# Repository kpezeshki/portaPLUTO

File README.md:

# portaPLUTO
### LINQS Hardware Hack Week 2026

This is a handheld microwave analyzer based on the PlutoSky, a variant of the ADALM-PLUTO SDR development platform. At a hardware level, it consists of a PlutoSky RF PCB, a system board, and user IO. The software integrates with Maia-SDR and iio to deliver basic microwave characterization functionality.

## Hardware

To build a portaPLUTO, you will need the following:

- a PlutoSky board. Buy one without the GPIO header, as you'll want pins of a different height
- a mainboard PCB. JLCPCB stocks most of the components, but minor SMT hand assembly is required
- an aluminum midplate. The Fusion file includes toolpaths for a Makera Carvera, but you can get this manufactured externally. This needs to be aluminum, not plastic, as it is used as a heatsink.
- an 18650 cell. Unprotected is OK. The max discharge you should expect is 1.5 A
- a CH320QV15A-T 3.2" TFT display. Adafruit resells these
- Assorted 3D printed components (backplate, display mount, knob). Some of these have versions intended for machining with toolpaths

## Software

The main software package is built around tezuka and maia-sdr, though rtl_433 and dump1090 are exposed in applications. The software consists of an FPGA image, a Zynq firmware image, and a Pi Pico firmware image: these vary from the tezuka defaults, so ensure you flash both.

Importantly, *the system must be powered before you plug the PlutoSky or Pico in to a computer!*

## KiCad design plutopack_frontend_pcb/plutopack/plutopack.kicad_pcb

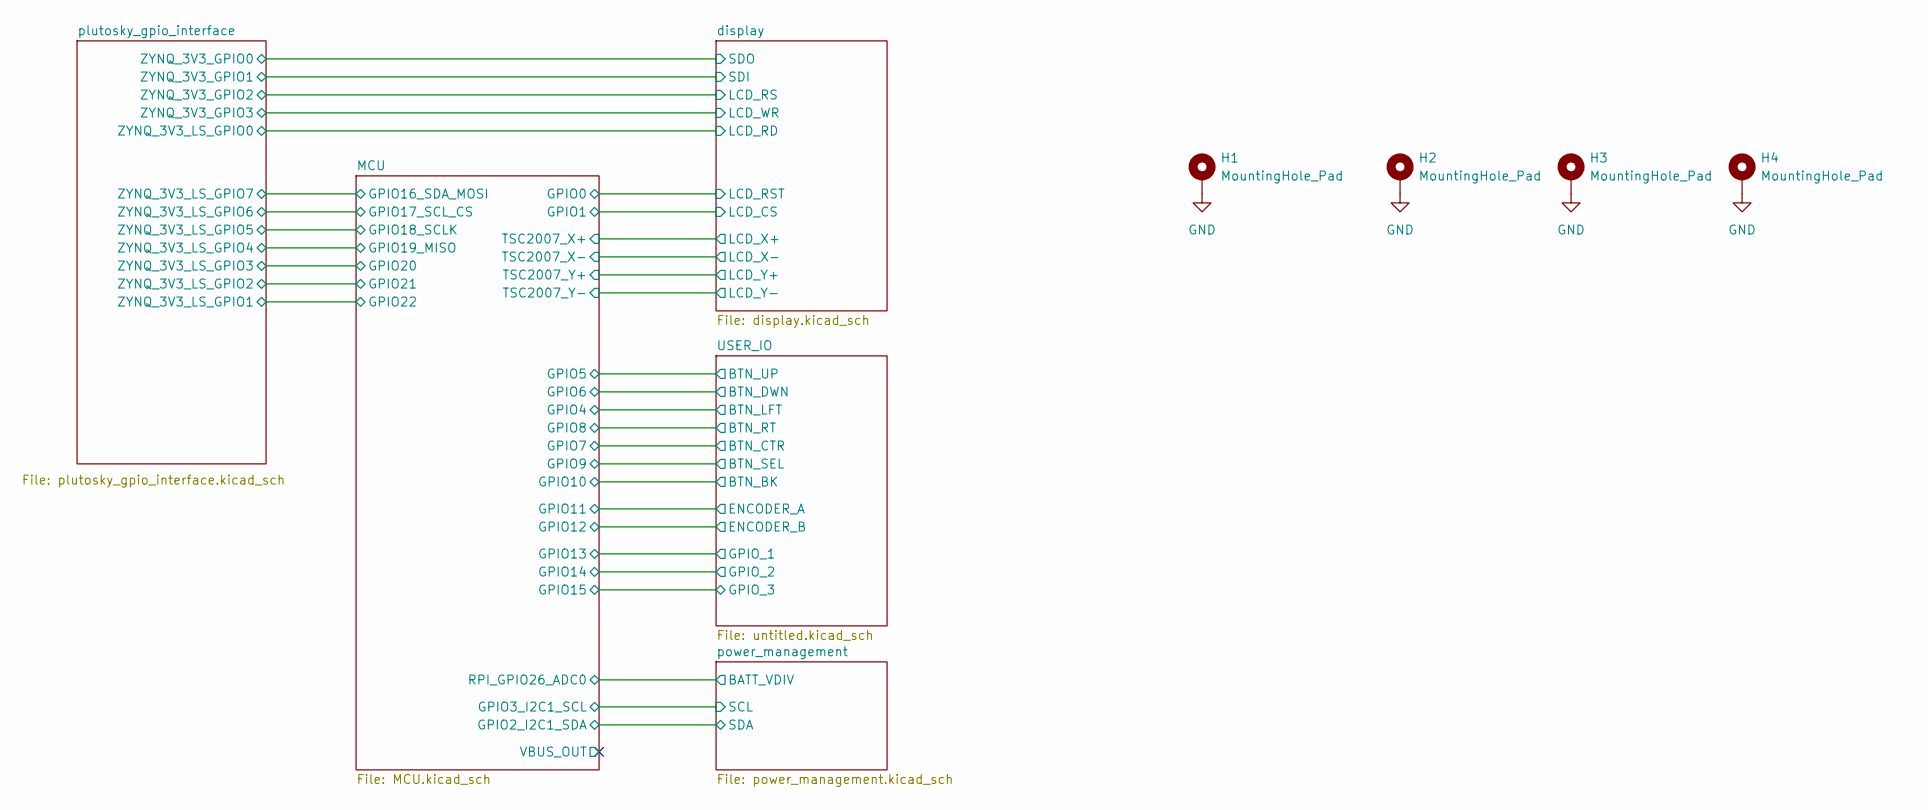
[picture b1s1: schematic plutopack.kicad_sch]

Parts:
H1, H2, H3, H4: MountingHole_Pad; MountingHole_3.2mm_M3_DIN965_Pad

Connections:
GND: H1.1, H2.1, H3.1, H4.1; also elsewhere on the board

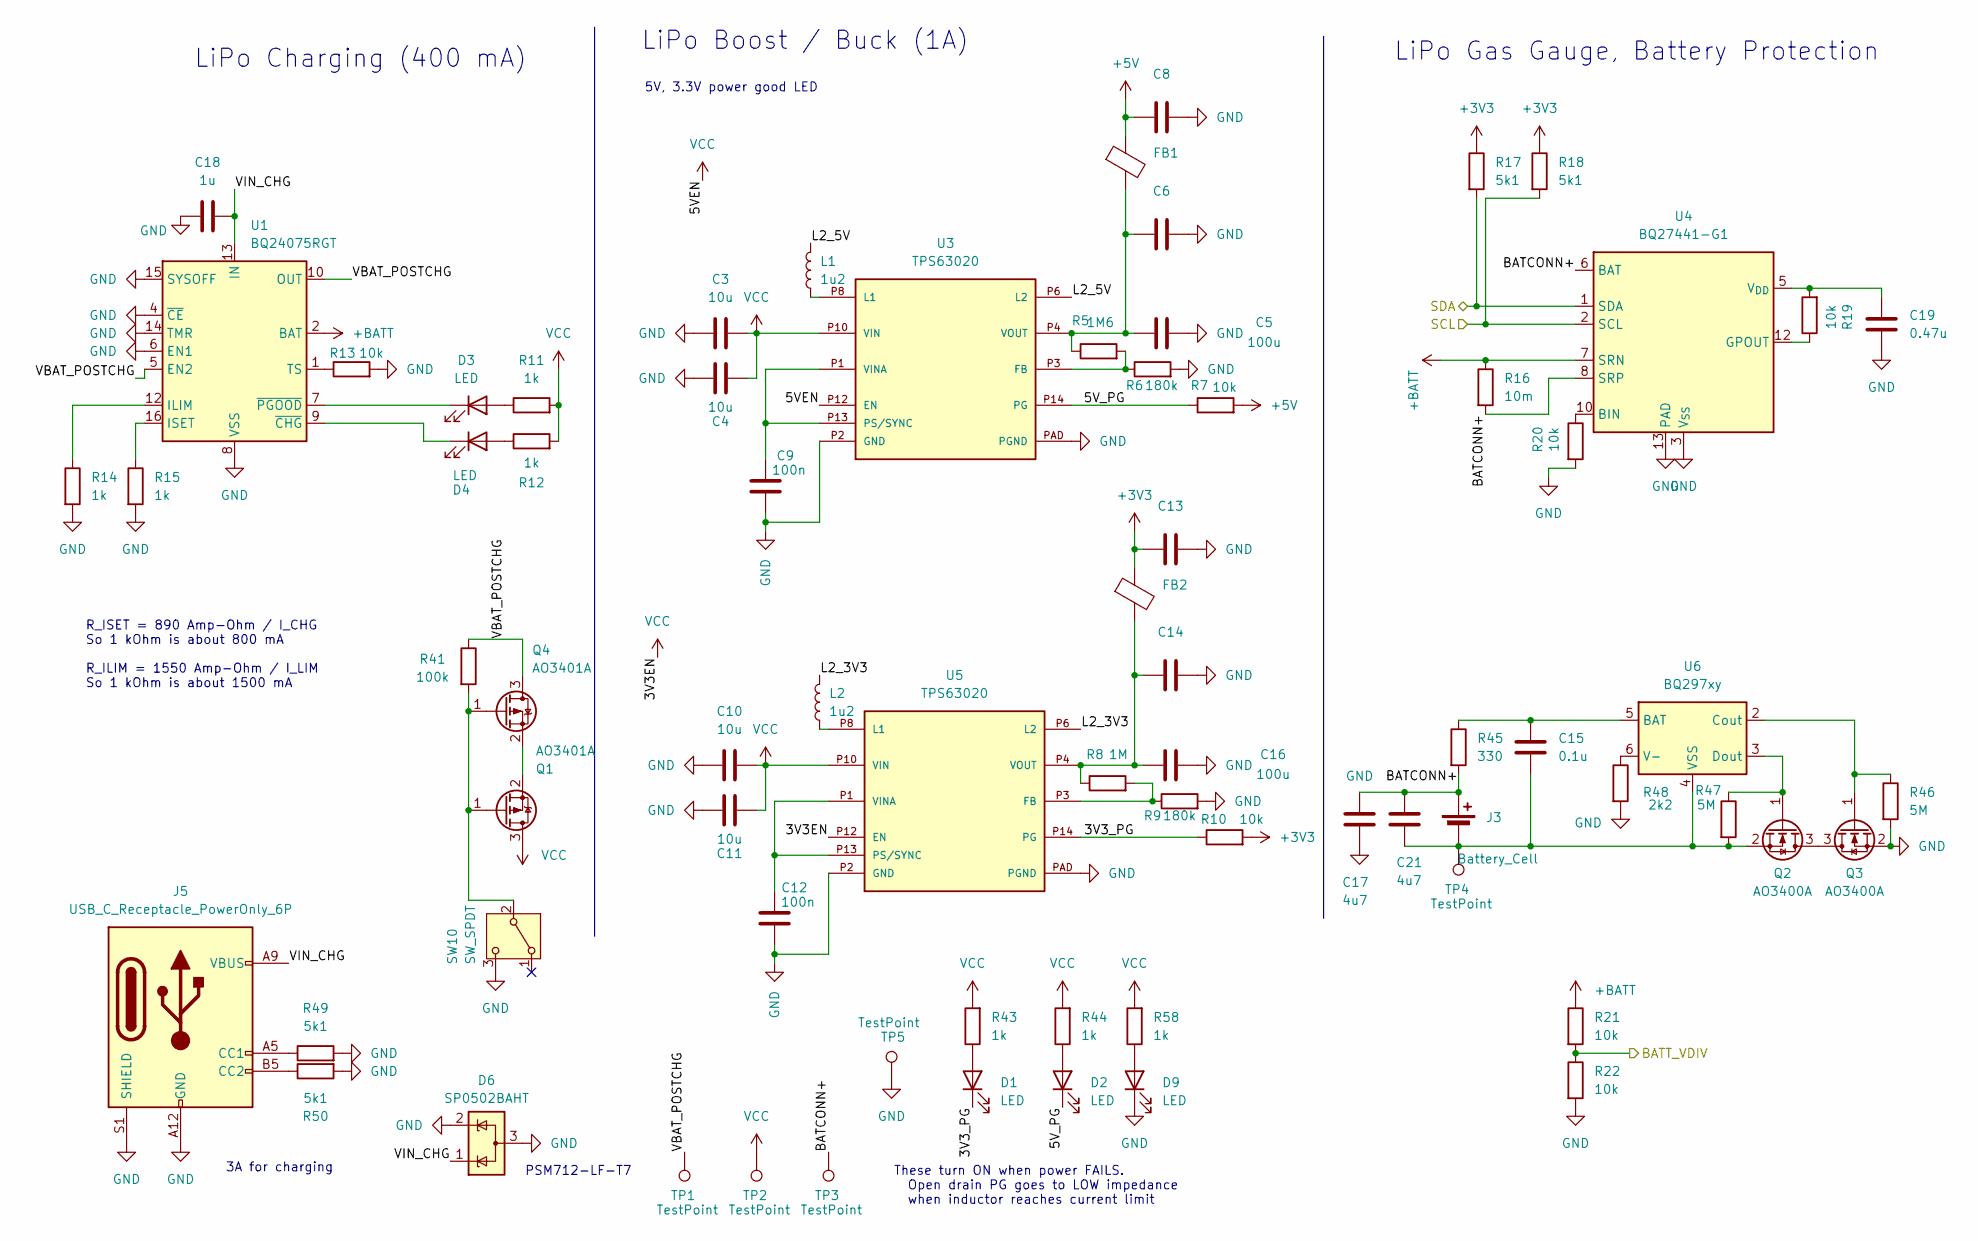
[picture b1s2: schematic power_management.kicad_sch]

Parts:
C3, C4, C10, C11: 10u; C_0603_1608Metric
C5, C16: 100u; CP_EIA-7343-31_Kemet-D
C6, C8, C13, C14: C_0603_1608Metric
C9, C12: 100n; C_0603_1608Metric
C15: 0.1u; C_0603_1608Metric
C17, C21: 4u7; C_0603_1608Metric
C18: 1u; C_0603_1608Metric
C19: 0.47u; C_0603_1608Metric
D1, D2, D3, D4, D9: LED; LED_0603_1608Metric
D6: SP0502BAHT; SOT-23
FB1, FB2: R_0603_1608Metric
J3: Battery_Cell; BatteryHolder_Keystone_1042_1x18650
J5: USB_C_Receptacle_PowerOnly_6P; USB_C_Receptacle_GCT_USB4125-xx-x-0190_6P_TopMnt_Horizontal
L1, L2: 1u2; L_12x12mm_H4.5mm
Q1, Q4: AO3401A; SOT-23
Q2, Q3: AO3400A; SOT-23
R5: 1M6; R_0603_1608Metric
R6, R9: 180k; R_0603_1608Metric
R7, R10, R13, R19, R20, R21, R22: 10k; R_0603_1608Metric
R8: 1M; R_0603_1608Metric
R11, R12, R14, R15, R43, R44, R58: 1k; R_0603_1608Metric
R16: 10m; R_0603_1608Metric
R17, R18, R49, R50: 5k1; R_0603_1608Metric
R41: 100k; R_0603_1608Metric
R45: 330; R_0603_1608Metric
R46, R47: 5M; R_0603_1608Metric
R48: 2k2; R_0603_1608Metric
SW10: SW_SPDT; SW_Slide_SPDT_Straight_CK_OS102011MS2Q
TP1, TP2, TP3, TP4, TP5: TestPoint; TestPoint_THTPad_D1.5mm_Drill0.7mm
U1: BQ24075RGT; VQFN-16-1EP_3x3mm_P0.5mm_EP1.6x1.6mm
U3, U5: TPS63020; QFN14_1
U4: BQ27441-G1; Texas_S-PDSO-N12
U6: BQ297xy; WSON-6_1.5x1.5mm_P0.5mm

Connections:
+3V3: C13.2, FB2.1, R10.2, R17.1, R18.1; also elsewhere on the board
+5V: C8.2, FB1.1, R7.2; also elsewhere on the board
+BATT: R16.1, R21.1, U1.2 (BAT), U1.3 (BAT), U4.7 (SRN)
/MCU/GPIO2_I2C1_SDA: R17.2, U4.1 (SDA); also elsewhere on the board
/MCU/GPIO3_I2C1_SCL: R18.2, U4.2 (SCL); also elsewhere on the board
/MCU/RPI_GPIO26_ADC0: R21.2, R22.1; also elsewhere on the board
/power_management/3V3_PG: D1.1 (K), R10.1, U5.P14 (PG)
/power_management/5V_PG: D2.1 (K), R7.1, U3.P14 (PG)
/power_management/BATCONN+: C17.2, C21.2, J3.1 (+), R16.2, R45.2, TP3.1, U4.6 (BAT), U4.8 (SRP)
/power_management/L2_3V3: L2.2, U5.P6 (L2), U5.P7 (L2)
/power_management/L2_5V: L1.2, U3.P6 (L2), U3.P7 (L2)
/power_management/VBAT_POSTCHG: Q4.3 (D), R41.1, TP1.1, U1.5 (EN2), U1.10 (OUT), U1.11 (OUT)
/power_management/VIN_CHG: C18.2, D6.1 (K), J5.A9 (VBUS), J5.B9 (VBUS), U1.13 (IN)
GND: C3.1, C4.1, C5.1, C6.1, C8.1, C9.1, C10.1, C11.1, C12.1, C13.1, C14.1, C16.1, C17.1, C18.1, C19.1, D6.2 (K), D6.3 (A), D9.1 (K), J5.A12 (GND), J5.B12 (GND), J5.S1 (SHIELD), Q3.2 (S), R6.2, R9.2, R13.2, R14.2, R15.2, R20.2, R22.2, R46.2, R48.2, R49.2, R50.2, SW10.3 (C), TP5.1, U1.4 (~CE), U1.6 (EN1), U1.8 (VSS), U1.14 (TMR), U1.15 (SYSOFF), U1.17 (VSS), U3.P2 (GND), U3.PAD (PGND), U4.3 (V_{SS}), U4.13 (PAD), U5.P2 (GND), U5.PAD (PGND); also elsewhere on the board
unnamed: C5.2, C6.2, FB1.2, R5.1, U3.P4 (VOUT), U3.P5 (VOUT)
unnamed: C14.2, C16.2, FB2.2, R8.1, U5.P4 (VOUT), U5.P5 (VOUT)
unnamed: D1.2 (A), R43.1
unnamed: D2.2 (A), R44.1
unnamed: D3.2 (A), R11.1
unnamed: D3.1 (K), U1.7 (~PGOOD)
unnamed: D4.2 (A), R12.1
unnamed: D4.1 (K), U1.9 (~CHG)
unnamed: D9.2 (A), R58.1
unnamed: C15.2, C21.1, J3.2 (-), Q2.2 (S), R47.2, TP4.1, U6.4 (VSS)
unnamed: J5.A5 (CC1), R49.1
unnamed: J5.B5 (CC2), R50.1
unnamed: L1.1, U3.P8 (L1), U3.P9 (L1)
unnamed: L2.1, U5.P8 (L1), U5.P9 (L1)
unnamed: Q1.1 (G), Q4.1 (G), R41.2, SW10.2 (B)
unnamed: Q1.2 (S), Q4.2 (S)
unnamed: Q2.3 (D), Q3.3 (D)
unnamed: Q2.1 (G), R47.1, U6.3 (Dout)
unnamed: Q3.1 (G), R46.1, U6.2 (Cout)
unnamed: R14.1, U1.12 (ILIM)
unnamed: R15.1, U1.16 (ISET)
unnamed: R13.1, U1.1 (TS)
unnamed: R5.2, R6.1, U3.P3 (FB)
unnamed: C9.2, U3.P1 (VINA), U3.P13 (PS/SYNC)
unnamed: R20.1, U4.10 (BIN)
unnamed: R19.1, U4.12 (GPOUT)
unnamed: C19.2, R19.2, U4.5 (V_{DD})
unnamed: R8.2, R9.1, U5.P3 (FB)
unnamed: C12.2, U5.P1 (VINA), U5.P13 (PS/SYNC)
unnamed: C15.1, R45.1, U6.5 (BAT)
unnamed: R48.1, U6.6 (V-)
VCC: C3.2, C4.2, C10.2, C11.2, Q1.3 (D), R11.2, R12.2, R43.2, R44.2, R58.2, TP2.1, U3.P10 (VIN), U3.P11 (VIN), U3.P12 (EN), U5.P10 (VIN), U5.P11 (VIN), U5.P12 (EN)

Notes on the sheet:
3A for charging
LiPo Gas Gauge, Battery Protection
5V, 3.3V power good LED
LiPo Charging (400 mA)
These turn ON when power FAILS. Open drain PG goes to LOW impedance when inductor reaches current limit
R_ILIM = 1550 Amp-Ohm / I_LIM So 1 kOhm is about 1500 mA
LiPo Boost / Buck (1A)
R_ISET = 890 Amp-Ohm / I_CHG So 1 kOhm is about 800 mA
PSM712-LF-T7

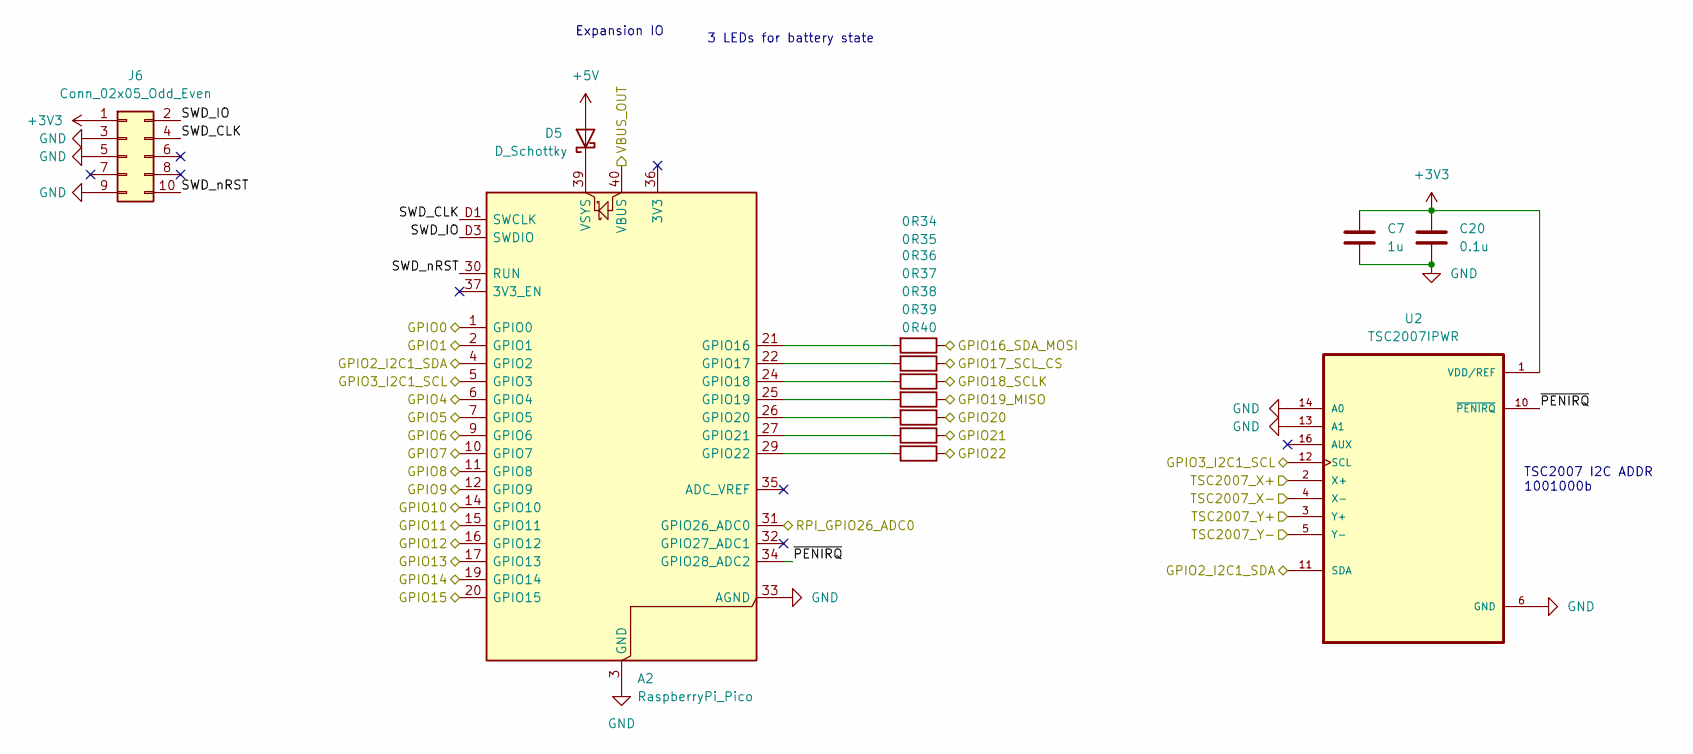
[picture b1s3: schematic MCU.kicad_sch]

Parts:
A2: RaspberryPi_Pico; RaspberryPi_Pico_SMD_HandSolder
C7: 1u; C_0603_1608Metric
C20: 0.1u; C_0603_1608Metric
D5: D_Schottky; D_SOD-123
J6: Conn_02x05_Odd_Even; PinSocket_2x05_P1.27mm_Vertical_SMD
R34, R35, R36, R37, R38, R39, R40: 0; R_0603_1608Metric
U2: TSC2007IPWR; SOP65P640X120-16N

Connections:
+3V3: C7.1, C20.2, J6.1, U2.1 (VDD/REF); also elsewhere on the board
+5V: D5.2 (A); also elsewhere on the board
/MCU/GPIO0: A2.1 (GPIO0); also elsewhere on the board
/MCU/GPIO1: A2.2 (GPIO1); also elsewhere on the board
/MCU/GPIO2_I2C1_SDA: A2.4 (GPIO2), U2.11 (SDA); also elsewhere on the board
/MCU/GPIO3_I2C1_SCL: A2.5 (GPIO3), U2.12 (SCL); also elsewhere on the board
/MCU/GPIO4: A2.6 (GPIO4); also elsewhere on the board
/MCU/GPIO5: A2.7 (GPIO5); also elsewhere on the board
/MCU/GPIO6: A2.9 (GPIO6); also elsewhere on the board
/MCU/GPIO7: A2.10 (GPIO7); also elsewhere on the board
/MCU/GPIO8: A2.11 (GPIO8); also elsewhere on the board
/MCU/GPIO9: A2.12 (GPIO9); also elsewhere on the board
/MCU/GPIO10: A2.14 (GPIO10); also elsewhere on the board
/MCU/GPIO11: A2.15 (GPIO11); also elsewhere on the board
/MCU/GPIO12: A2.16 (GPIO12); also elsewhere on the board
/MCU/GPIO13: A2.17 (GPIO13); also elsewhere on the board
/MCU/GPIO14: A2.19 (GPIO14); also elsewhere on the board
/MCU/GPIO15: A2.20 (GPIO15); also elsewhere on the board
/MCU/GPIO16_SDA_MOSI: R34.1; also elsewhere on the board
/MCU/GPIO17_SCL_CS: R35.1; also elsewhere on the board
/MCU/GPIO18_SCLK: R36.1; also elsewhere on the board
/MCU/GPIO19_MISO: R37.1; also elsewhere on the board
/MCU/GPIO20: R38.1; also elsewhere on the board
/MCU/GPIO21: R39.1; also elsewhere on the board
/MCU/GPIO22: R40.1; also elsewhere on the board
/MCU/RPI_GPIO26_ADC0: A2.31 (GPIO26_ADC0); also elsewhere on the board
/MCU/SWD_CLK: A2.D1 (SWCLK), J6.4
/MCU/SWD_IO: A2.D3 (SWDIO), J6.2
/MCU/SWD_nRST: A2.30 (RUN), J6.10
/MCU/TSC2007_X+: U2.2 (X+); also elsewhere on the board
/MCU/TSC2007_X-: U2.4 (X-); also elsewhere on the board
/MCU/TSC2007_Y+: U2.3 (Y+); also elsewhere on the board
/MCU/TSC2007_Y-: U2.5 (Y-); also elsewhere on the board
/MCU/VBUS_OUT: A2.40 (VBUS)
/MCU/~PENIRQ: A2.34 (GPIO28_ADC2), U2.10 (~PENIRQ)
GND: A2.3 (GND), A2.8 (GND), A2.13 (GND), A2.18 (GND), A2.23 (GND), A2.28 (GND), A2.33 (AGND), A2.38 (GND), A2.D2 (GND), C7.2, C20.1, J6.3, J6.5, J6.9, U2.6 (GND), U2.13 (A1), U2.14 (A0); also elsewhere on the board
unnamed: A2.21 (GPIO16), R34.2
unnamed: A2.22 (GPIO17), R35.2
unnamed: A2.24 (GPIO18), R36.2
unnamed: A2.25 (GPIO19), R37.2
unnamed: A2.26 (GPIO20), R38.2
unnamed: A2.27 (GPIO21), R39.2
unnamed: A2.29 (GPIO22), R40.2
unnamed: A2.39 (VSYS), D5.1 (K)

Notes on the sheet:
Expansion IO
3 LEDs for battery state
TSC2007 I2C ADDR 1001000b

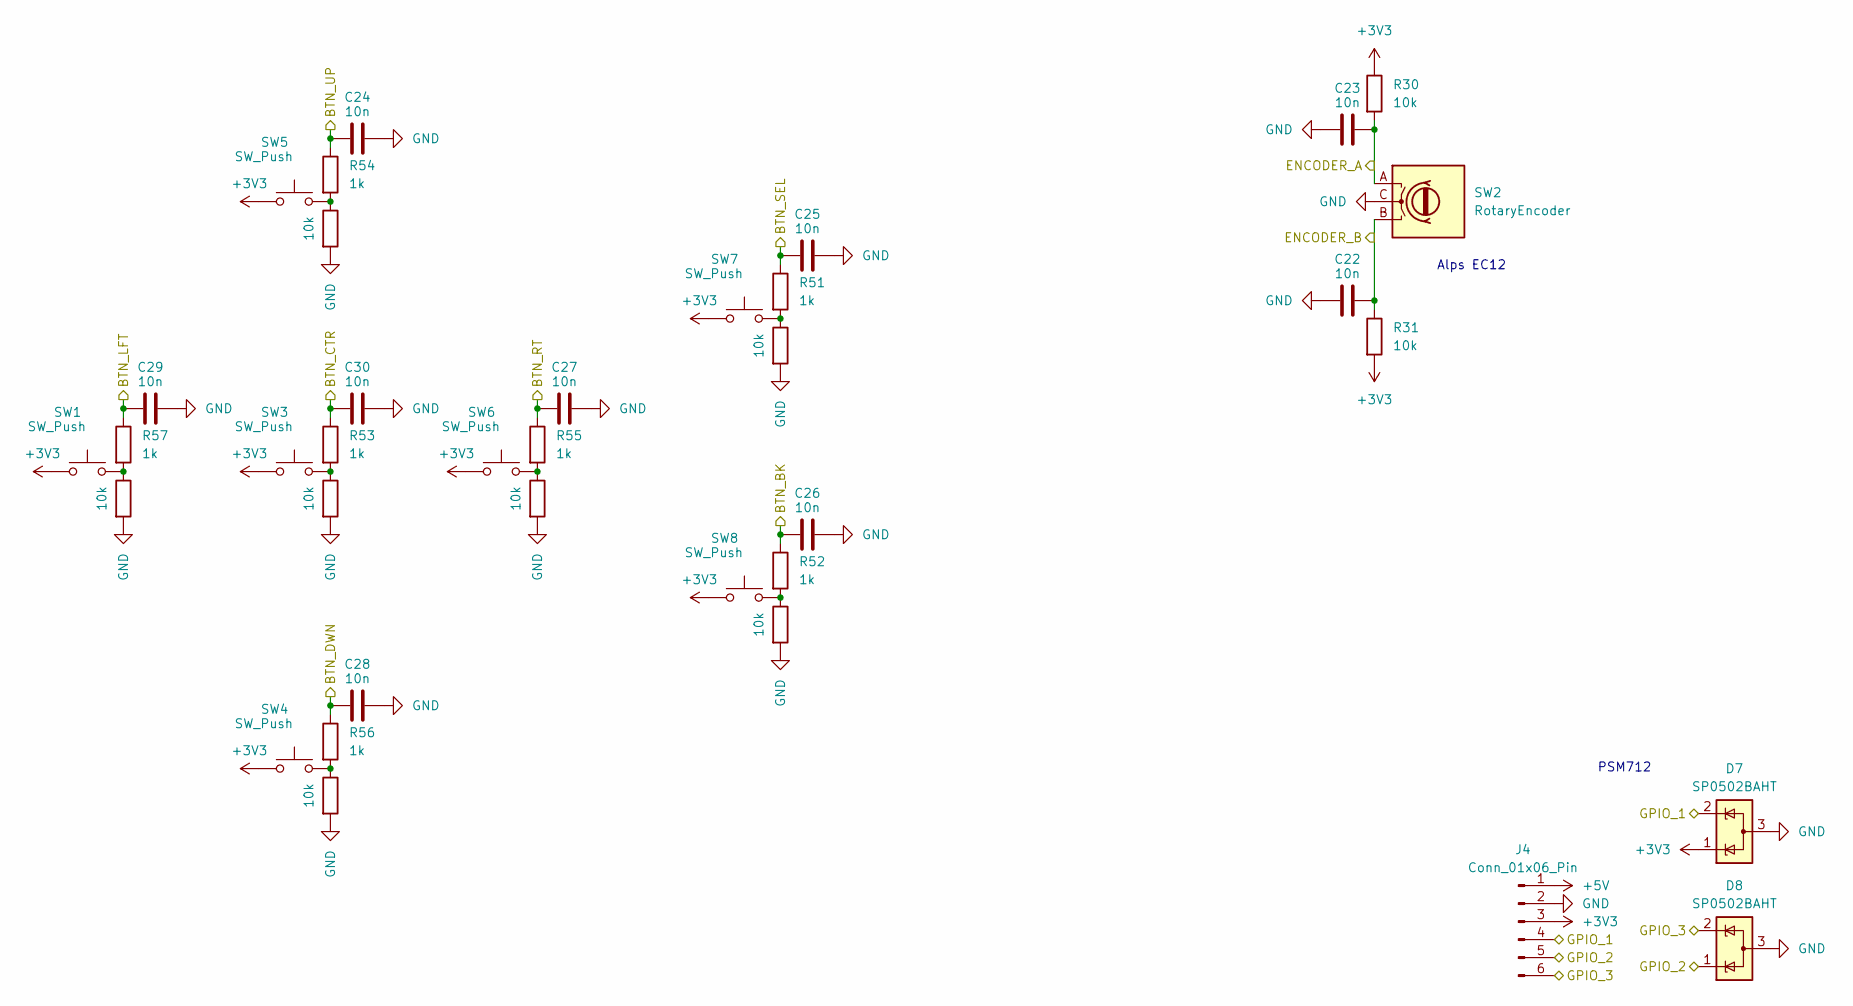
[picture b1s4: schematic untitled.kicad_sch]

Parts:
C22, C23, C24, C25, C26, C27, C28, C29, C30: 10n; C_0603_1608Metric
D7, D8: SP0502BAHT; SOT-23
J4: Conn_01x06_Pin; PinSocket_1x06_P2.54mm_Horizontal
R23, R24, R25, R26, R27, R28, R29, R30, R31: 10k; R_0603_1608Metric
R51, R52, R53, R54, R55, R56, R57: 1k; R_0603_1608Metric
SW1, SW3, SW4, SW5, SW6, SW7, SW8: SW_Push; SW_Push_1P1T_NO_CK_KSC6xxG
SW2: RotaryEncoder; RotaryEncoder_Alps_EC12E_Vertical_H20mm

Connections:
+3V3: D7.1 (K), J4.3, R30.1, R31.2, SW1.1, SW3.1, SW4.1, SW5.1, SW6.1, SW7.1, SW8.1; also elsewhere on the board
+5V: J4.1; also elsewhere on the board
/MCU/GPIO4: C29.1, R57.1; also elsewhere on the board
/MCU/GPIO5: C24.1, R54.1; also elsewhere on the board
/MCU/GPIO6: C28.1, R56.1; also elsewhere on the board
/MCU/GPIO7: C30.1, R53.1; also elsewhere on the board
/MCU/GPIO8: C27.1, R55.1; also elsewhere on the board
/MCU/GPIO9: C25.1, R51.1; also elsewhere on the board
/MCU/GPIO10: C26.1, R52.1; also elsewhere on the board
/MCU/GPIO11: C23.2, R30.2, SW2.A; also elsewhere on the board
/MCU/GPIO12: C22.2, R31.1, SW2.B; also elsewhere on the board
/MCU/GPIO13: D7.2 (K), J4.4; also elsewhere on the board
/MCU/GPIO14: D8.1 (K), J4.5; also elsewhere on the board
/MCU/GPIO15: D8.2 (K), J4.6; also elsewhere on the board
GND: C22.1, C23.1, C24.2, C25.2, C26.2, C27.2, C28.2, C29.2, C30.2, D7.3 (A), D8.3 (A), J4.2, R23.2, R24.2, R25.2, R26.2, R27.2, R28.2, R29.2, SW2.C; also elsewhere on the board
unnamed: R23.1, R53.2, SW3.2
unnamed: R24.1, R56.2, SW4.2
unnamed: R25.1, R54.2, SW5.2
unnamed: R26.1, R55.2, SW6.2
unnamed: R27.1, R57.2, SW1.2
unnamed: R28.1, R51.2, SW7.2
unnamed: R29.1, R52.2, SW8.2

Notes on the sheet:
PSM712
Alps EC12

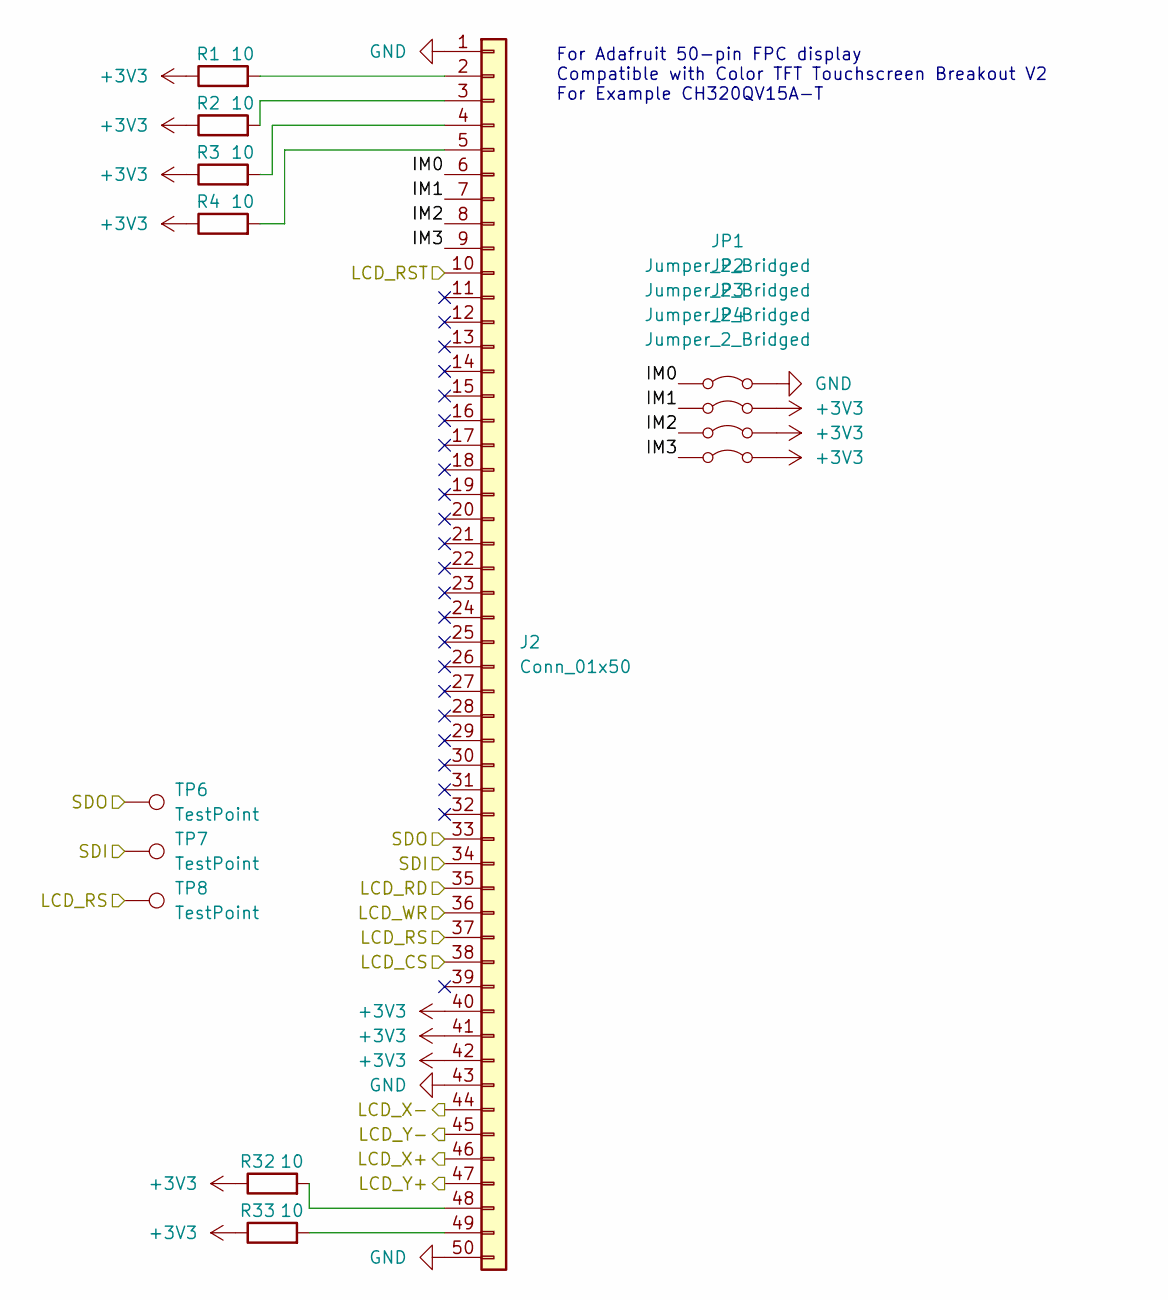
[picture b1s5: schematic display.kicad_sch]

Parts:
J2: Conn_01x50; Amphenol_F32Q-1A7x1-11050_1x50-1MP_P0.5mm_Horizontal
JP1, JP2, JP3, JP4: Jumper_2_Bridged; SolderJumper-2_P1.3mm_Bridged_RoundedPad1.0x1.5mm
R1, R2, R3, R4, R32, R33: 10; R_0603_1608Metric
TP6, TP7, TP8: TestPoint; TestPoint_Pad_D1.0mm

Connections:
+3V3: J2.40, J2.41, J2.42, JP2.2 (B), JP3.2 (B), JP4.2 (B), R1.1, R2.1, R3.1, R4.1, R32.1, R33.1; also elsewhere on the board
/MCU/GPIO0: J2.10; also elsewhere on the board
/MCU/GPIO1: J2.38; also elsewhere on the board
/MCU/TSC2007_X+: J2.46; also elsewhere on the board
/MCU/TSC2007_X-: J2.44; also elsewhere on the board
/MCU/TSC2007_Y+: J2.47; also elsewhere on the board
/MCU/TSC2007_Y-: J2.45; also elsewhere on the board
/display/IM0: J2.6, JP1.1 (A)
/display/IM1: J2.7, JP2.1 (A)
/display/IM2: J2.8, JP3.1 (A)
/display/IM3: J2.9, JP4.1 (A)
/display/LCD_RD: J2.35; also elsewhere on the board
/display/LCD_RS: J2.37, TP8.1; also elsewhere on the board
/display/LCD_WR: J2.36; also elsewhere on the board
/display/SDI: J2.34, TP7.1; also elsewhere on the board
/display/SDO: J2.33, TP6.1; also elsewhere on the board
GND: J2.1, J2.43, J2.50, JP1.2 (B); also elsewhere on the board
unnamed: J2.2, R1.2
unnamed: J2.3, R2.2
unnamed: J2.4, R3.2
unnamed: J2.5, R4.2
unnamed: J2.48, R32.2
unnamed: J2.49, R33.2

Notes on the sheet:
For Adafruit 50-pin FPC display Compatible with Color TFT Touchscreen Breakout V2 For Example CH320QV15A-T

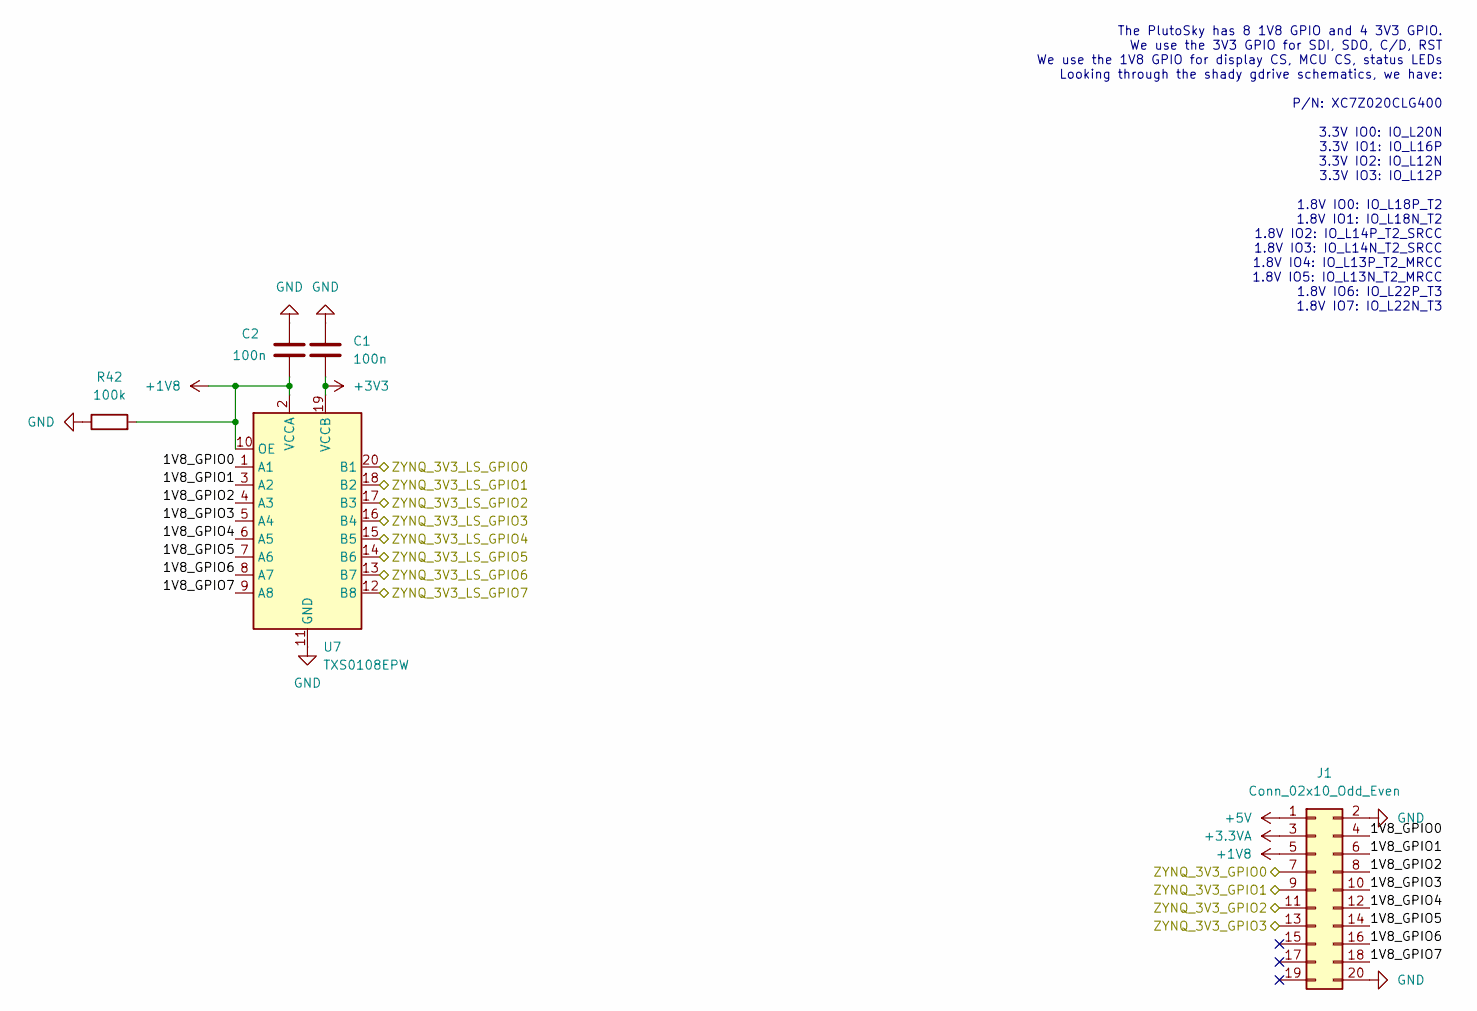
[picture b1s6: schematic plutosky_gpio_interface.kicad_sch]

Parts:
C1, C2: 100n; C_0603_1608Metric
J1: Conn_02x10_Odd_Even; PinHeader_2x10_P2.54mm_Vertical
R42: 100k; R_0603_1608Metric
U7: TXS0108EPW; TSSOP-20_4.4x6.5mm_P0.65mm

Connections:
+1V8: C2.1, J1.5, R42.2, U7.2 (VCCA), U7.10 (OE)
+3.3VA: J1.3
+3V3: C1.2, U7.19 (VCCB); also elsewhere on the board
+5V: J1.1; also elsewhere on the board
/MCU/GPIO16_SDA_MOSI: U7.12 (B8); also elsewhere on the board
/MCU/GPIO17_SCL_CS: U7.13 (B7); also elsewhere on the board
/MCU/GPIO18_SCLK: U7.14 (B6); also elsewhere on the board
/MCU/GPIO19_MISO: U7.15 (B5); also elsewhere on the board
/MCU/GPIO20: U7.16 (B4); also elsewhere on the board
/MCU/GPIO21: U7.17 (B3); also elsewhere on the board
/MCU/GPIO22: U7.18 (B2); also elsewhere on the board
/display/LCD_RD: U7.20 (B1); also elsewhere on the board
/display/LCD_RS: J1.11; also elsewhere on the board
/display/LCD_WR: J1.13; also elsewhere on the board
/display/SDI: J1.9; also elsewhere on the board
/display/SDO: J1.7; also elsewhere on the board
/plutosky_gpio_interface/1V8_GPIO0: J1.4, U7.1 (A1)
/plutosky_gpio_interface/1V8_GPIO1: J1.6, U7.3 (A2)
/plutosky_gpio_interface/1V8_GPIO2: J1.8, U7.4 (A3)
/plutosky_gpio_interface/1V8_GPIO3: J1.10, U7.5 (A4)
/plutosky_gpio_interface/1V8_GPIO4: J1.12, U7.6 (A5)
/plutosky_gpio_interface/1V8_GPIO5: J1.14, U7.7 (A6)
/plutosky_gpio_interface/1V8_GPIO6: J1.16, U7.8 (A7)
/plutosky_gpio_interface/1V8_GPIO7: J1.18, U7.9 (A8)
GND: C1.1, C2.2, J1.2, J1.20, R42.1, U7.11 (GND); also elsewhere on the board

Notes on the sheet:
The PlutoSky has 8 1V8 GPIO and 4 3V3 GPIO. We use the 3V3 GPIO for SDI, SDO, C/D, RST We use the 1V8 GPIO for display CS, MCU CS, status LEDs Looking through the shady gdrive schematics, we have: P/N: XC7Z020CLG400 3.3V IO0: IO_L20N 3.3V IO1: IO_L16P 3.3V IO2: IO_L12N 3.3V IO3: IO_L12P 1.8V IO0: I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

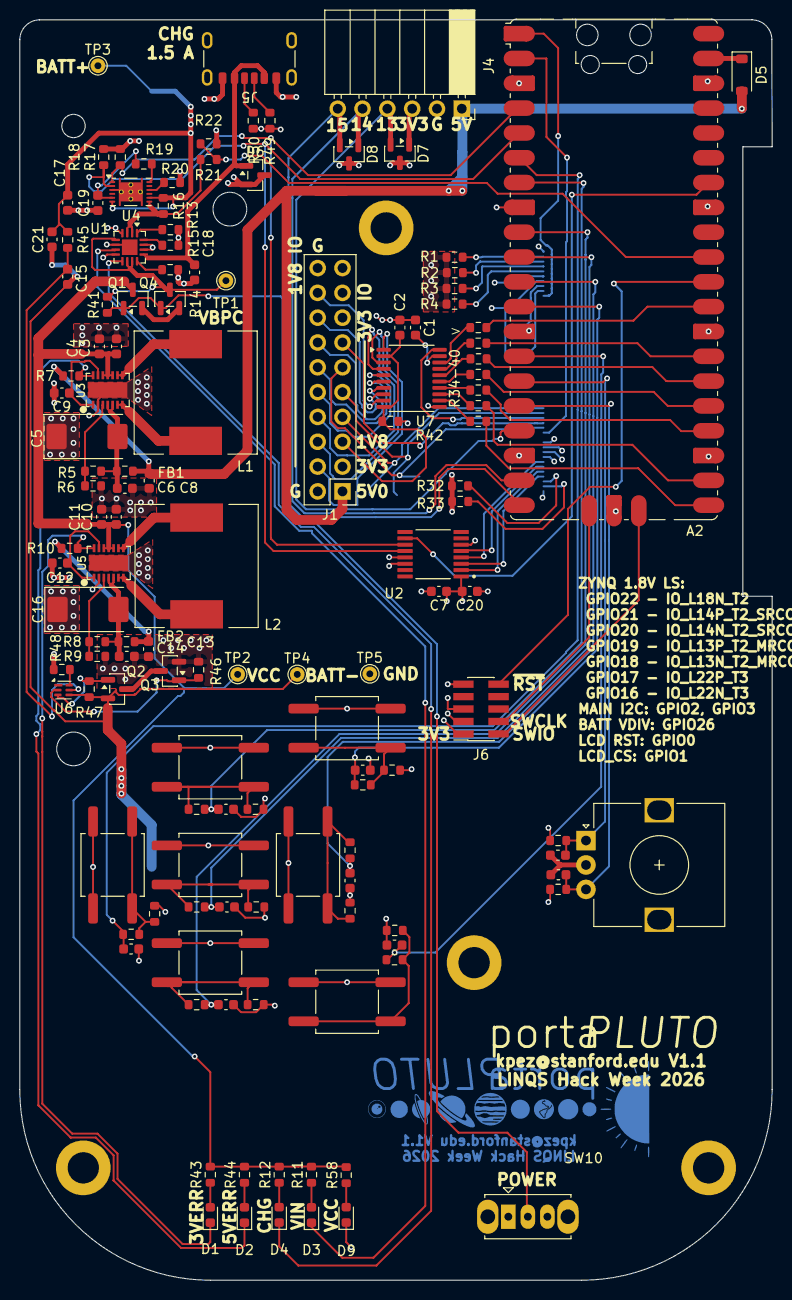
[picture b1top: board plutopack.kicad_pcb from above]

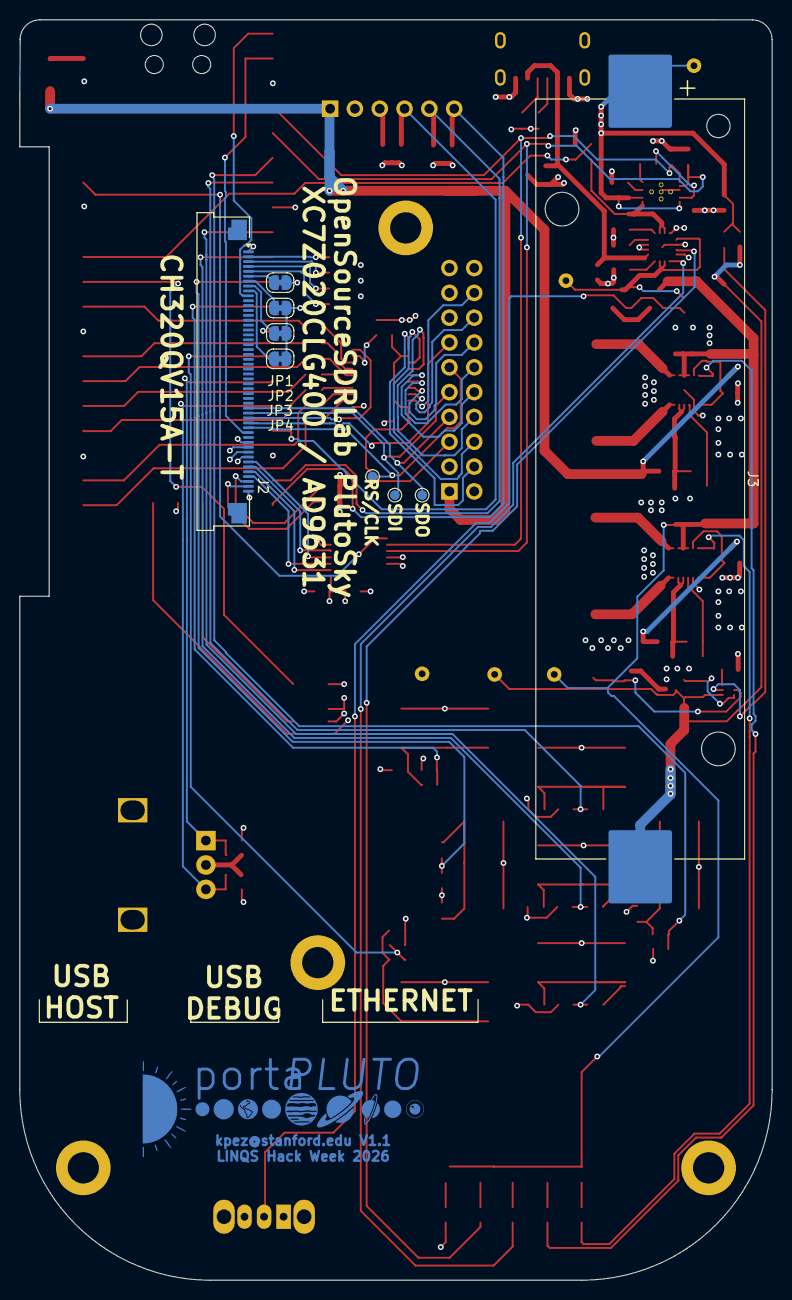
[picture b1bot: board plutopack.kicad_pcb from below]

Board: 4 copper layers, 77.0 x 129.0 mm, 144 parts (9 on the bottom side), 114 nets.

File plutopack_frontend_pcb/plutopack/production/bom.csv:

Designator,Footprint,Quantity,Value,LCSC Part #
A2,RaspberryPi_Pico_SMD_HandSolder,1,RaspberryPi_Pico,
"C1, C12, C2, C9",0603,4,100n,
"C10, C11, C3, C4",0603,4,10u,
"C13, C14, C6, C8, FB1, FB2",0603,6,~,
"C15, C20",0603,2,0.1u,
"C16, C5",CP_EIA-7343-31_Kemet-D,2,100u,
"C17, C21",0603,2,4u7,
"C18, C7",0603,2,1u,
C19,0603,1,0.47u,
"C22, C23, C24, C25, C26, C27, C28, C29, C30",0603,9,10n,
"D1, D2, D3, D4, D9",0603,5,LED,
D5,D_SOD-123,1,D_Schottky,
"D6, D7, D8",SOT-23,3,SP0502BAHT,
J1,PinHeader_2x10_P2.54mm_Vertical,1,Conn_02x10_Odd_Even,
J2,Amphenol_F32Q-1A7x1-11050_1x50-1MP_P0.5mm_Horizontal,1,Conn_01x50,
J3,BatteryHolder_Keystone_1042_1x18650,1,Battery_Cell,
J4,PinSocket_1x06_P2.54mm_Horizontal,1,Conn_01x06_Pin,
J5,USB_C_Receptacle_GCT_USB4125-xx-x-0190_6P_TopMnt_Horizontal,1,USB_C_Receptacle_PowerOnly_6P,
J6,PinSocket_2x05_P1.27mm_Vertical_SMD,1,Conn_02x05_Odd_Even,
"JP1, JP2, JP3, JP4",SolderJumper-2_P1.3mm_Bridged_RoundedPad1.0x1.5mm,4,Jumper_2_Bridged,
"L1, L2",L_12x12mm_H4.5mm,2,1u2,
"Q1, Q4",SOT-23,2,AO3401A,
"Q2, Q3",SOT-23,2,AO3400A,
"R1, R2, R3, R32, R33, R4",0603,6,10,
"R10, R13, R19, R20, R21, R22, R23, R24, R25, R26, R27, R28, R29, R30, R31, R7",0603,16,10k,
"R11, R12, R14, R15, R43, R44, R51, R52, R53, R54, R55, R56, R57, R58",0603,14,1k,
R16,0603,1,10m,
"R17, R18, R49, R50",0603,4,5k1,
"R34, R35, R36, R37, R38, R39, R40",0603,7,0,
"R41, R42",0603,2,100k,
R45,0603,1,330,
"R46, R47",0603,2,5M,
R48,0603,1,2k2,
R5,0603,1,1M6,
"R6, R9",0603,2,180k,
R8,0603,1,1M,
"SW1, SW3, SW4, SW5, SW6, SW7, SW8",SW_Push_1P1T_NO_CK_KSC6xxG,7,SW_Push,
SW10,SW_Slide_SPDT_Straight_CK_OS102011MS2Q,1,SW_SPDT,
SW2,RotaryEncoder_Alps_EC12E_Vertical_H20mm,1,RotaryEncoder,
"TP1, TP2, TP3, TP4, TP5",TestPoint_THTPad_D1.5mm_Drill0.7mm,5,TestPoint,
"TP6, TP7, TP8",TestPoint_Pad_D1.0mm,3,TestPoint,
U1,VQFN-16-1EP_3x3mm_P0.5mm_EP1.6x1.6mm,1,BQ24075RGT,
U2,SOP65P640X120-16N,1,TSC2007IPWR,
"U3, U5",QFN14_1,2,TPS63020,
U4,Texas_S-PDSO-N12,1,BQ27441-G1,
U6,WSON-6_1.5x1.5mm_P0.5mm,1,BQ297xy,
U7,TSSOP-20_4.4x6.5mm_P0.65mm,1,TXS0108EPW,
